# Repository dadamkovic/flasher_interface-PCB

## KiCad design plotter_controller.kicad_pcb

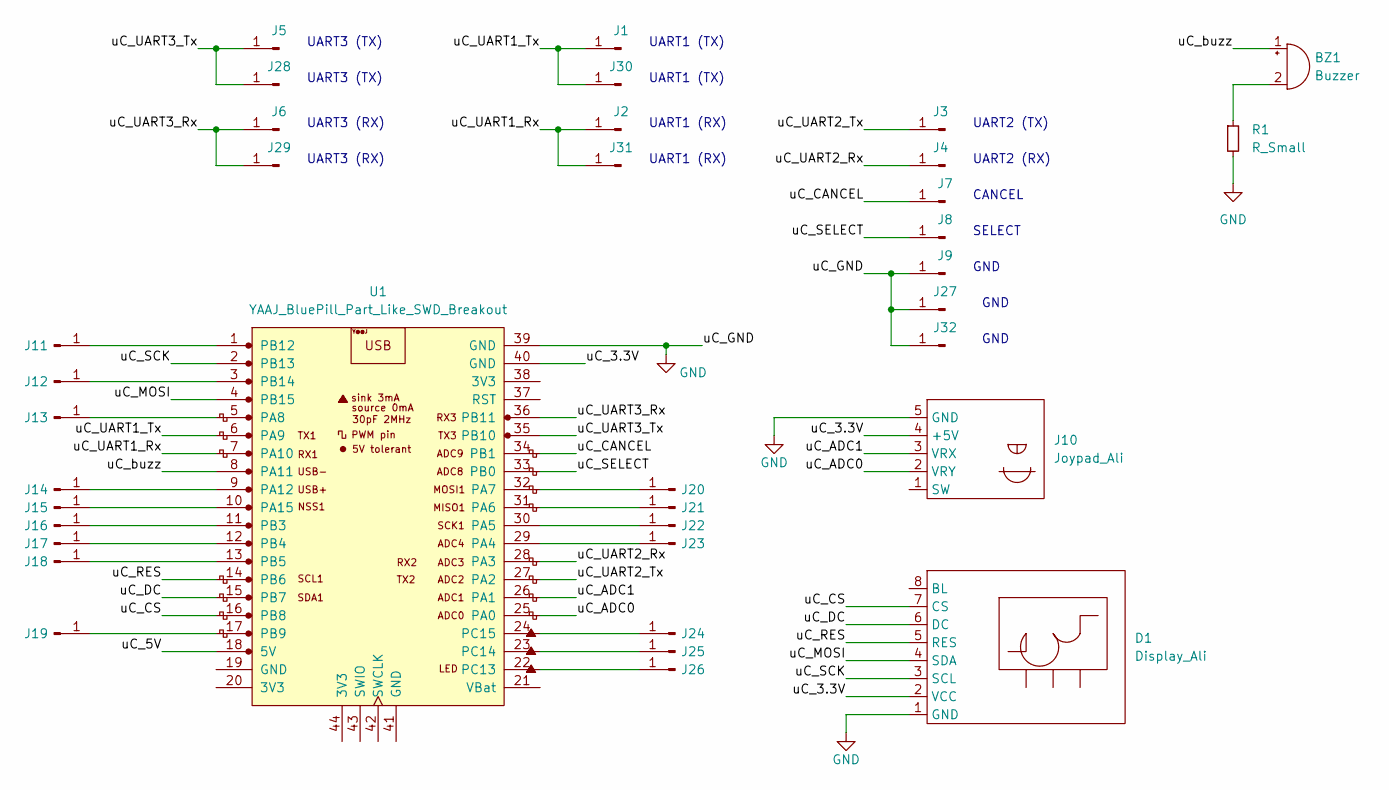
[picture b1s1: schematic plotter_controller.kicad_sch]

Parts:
BZ1: Buzzer; Buzzer_Murata_PKMCS0909E
D1: Display_Ali; Display_Ali (ST7735)
J1, J2, J3, J4, J5, J6, J7, J8, J9, J11, J12, J13, J14, J15, J16, J17, J18, J19, J20, J21, J22, J23, J24, J25, J26, J27, J28, J29, J30, J31, J32: Conn_01x01_Male; PinHeader_1x01_P2.54mm_Vertical
J10: Joypad_Ali
R1: R_Small; R_0805_2012Metric_Pad1.20x1.40mm_HandSolder
U1: YAAJ_BluePill_Part_Like_SWD_Breakout; YAAJ_BluePill_SWD_1

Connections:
/uC_3.3V: D1.2 (VCC), J10.4 (+5V), U1.40 (GND)
/uC_5V: U1.18 (5V)
/uC_ADC0: J10.2 (VRY), U1.25 (PA0)
/uC_ADC1: J10.3 (VRX), U1.26 (PA1)
/uC_CANCEL: J7.1, U1.34 (PB1)
/uC_CS: D1.7 (CS), U1.16 (PB8)
/uC_DC: D1.6 (DC), U1.15 (PB7)
/uC_MOSI: D1.4 (SDA), U1.4 (PB15)
/uC_RES: D1.5 (RES), U1.14 (PB6)
/uC_SCK: D1.3 (SCL), U1.2 (PB13)
/uC_SELECT: J8.1, U1.33 (PB0)
/uC_UART1_Rx: J2.1, J31.1, U1.7 (PA10)
/uC_UART1_Tx: J1.1, J30.1, U1.6 (PA9)
/uC_UART2_Rx: J4.1, U1.28 (PA3)
/uC_UART2_Tx: J3.1, U1.27 (PA2)
/uC_UART3_Rx: J6.1, J29.1, U1.36 (PB11)
/uC_UART3_Tx: J5.1, J28.1, U1.35 (PB10)
/uC_buzz: BZ1.1 (-), U1.8 (PA11)
GND: D1.1 (GND), J9.1, J10.5 (GND), J27.1, J32.1, R1.2, U1.39 (GND)
unnamed: BZ1.2 (+), R1.1
unnamed: J11.1, U1.1 (PB12)
unnamed: J12.1, U1.3 (PB14)
unnamed: J13.1, U1.5 (PA8)
unnamed: J14.1, U1.9 (PA12)
unnamed: J15.1, U1.10 (PA15)
unnamed: J16.1, U1.11 (PB3)
unnamed: J17.1, U1.12 (PB4)
unnamed: J18.1, U1.13 (PB5)
unnamed: J19.1, U1.17 (PB9)
unnamed: J20.1, U1.32 (PA7)
unnamed: J21.1, U1.31 (PA6)
unnamed: J22.1, U1.30 (PA5)
unnamed: J23.1, U1.29 (PA4)
unnamed: J24.1, U1.24 (PC15)
unnamed: J25.1, U1.23 (PC14)
unnamed: J26.1, U1.22 (PC13)

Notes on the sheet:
UART1 (RX)
GND
UART1 (TX)
UART3 (RX)
SELECT
UART3 (TX)
UART2 (RX)
UART2 (TX)
CANCEL

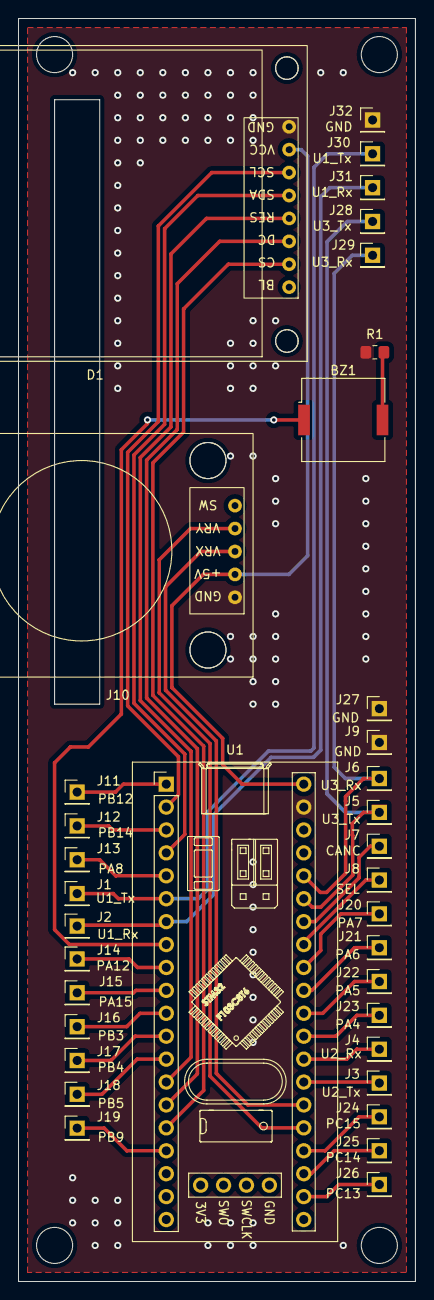
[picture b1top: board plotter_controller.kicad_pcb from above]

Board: 2 copper layers, 44.0 x 140.0 mm, 36 parts (0 on the bottom side), 35 nets.

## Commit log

2023-04-01 Separated into its own git repo.
